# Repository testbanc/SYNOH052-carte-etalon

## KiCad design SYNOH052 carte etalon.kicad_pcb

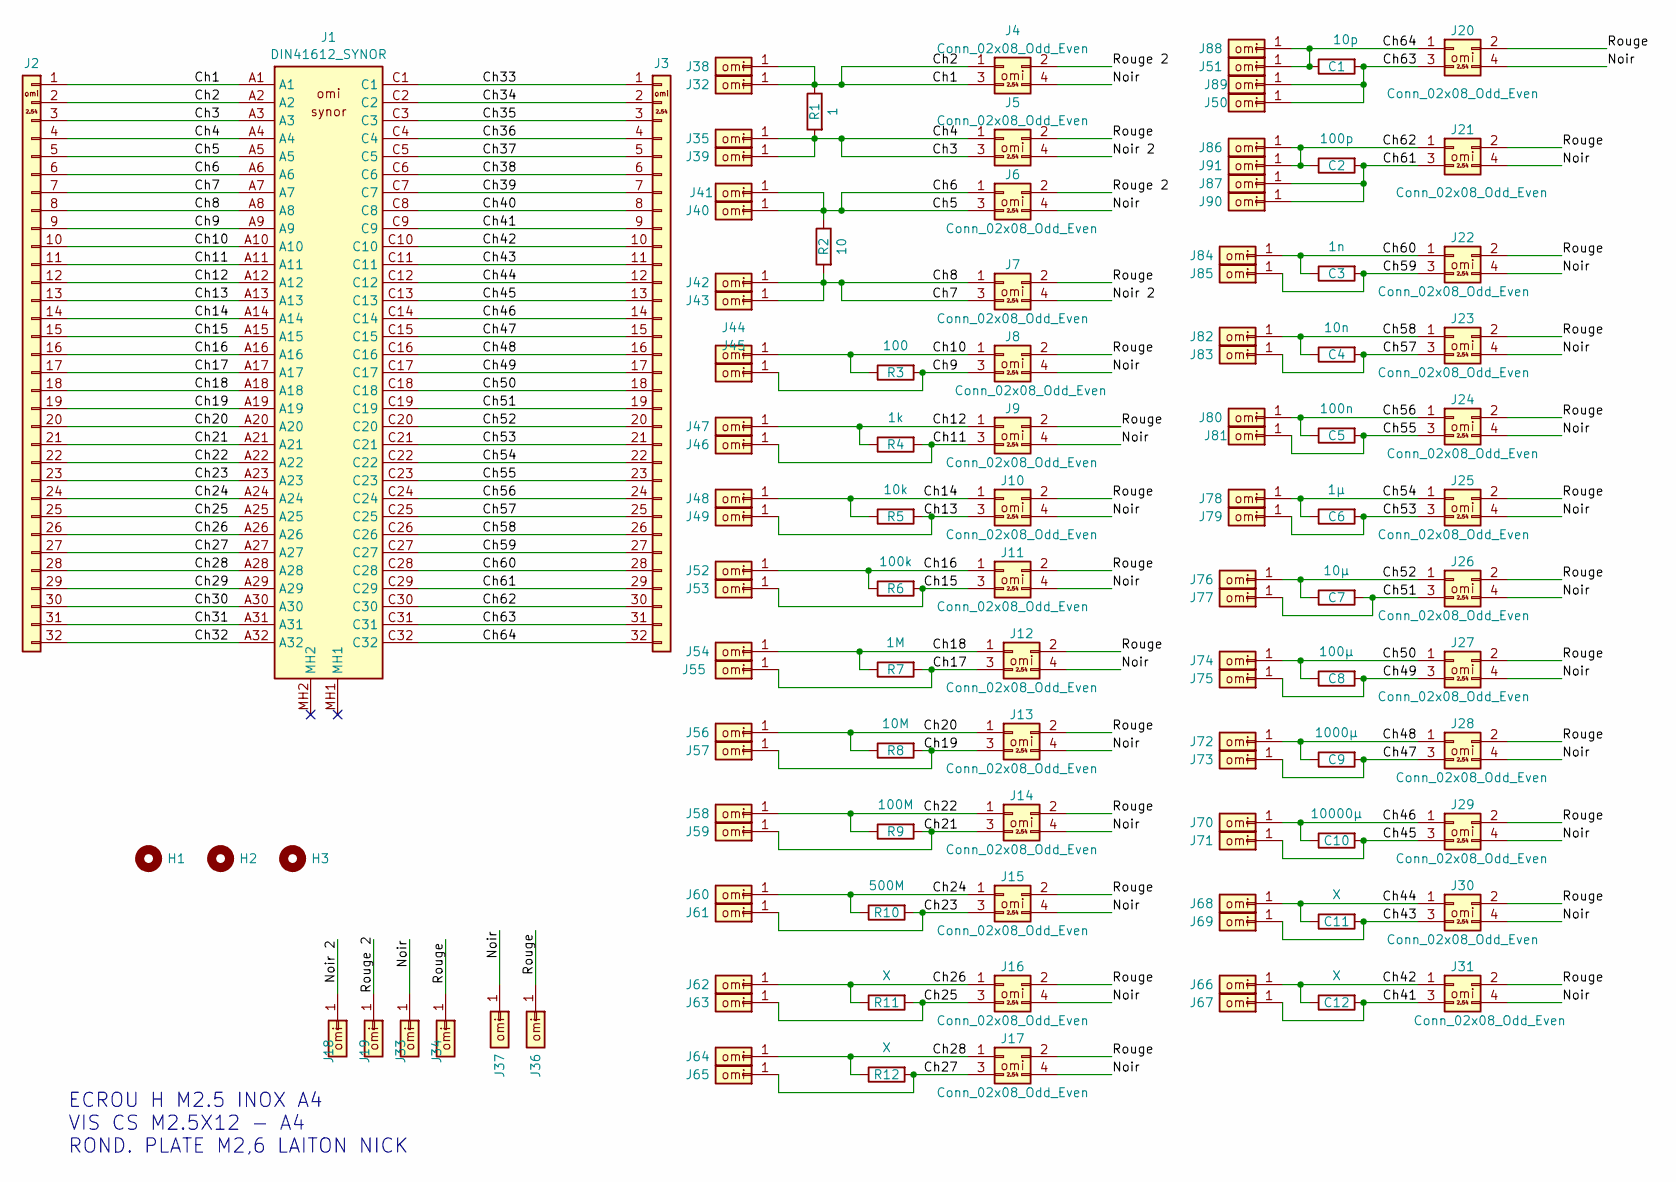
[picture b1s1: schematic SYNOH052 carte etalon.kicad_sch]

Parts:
C1: 10p; C_1206_3216Metric_Pad1.33x1.80mm_HandSolder
C2: 100p; C_1206_3216Metric_Pad1.33x1.80mm_HandSolder
C3: 1n; C_1206_3216Metric_Pad1.33x1.80mm_HandSolder
C4: 10n; C_1206_3216Metric_Pad1.33x1.80mm_HandSolder
C5: 100n; C_1206_3216Metric_Pad1.33x1.80mm_HandSolder
C6: 1µ; C_1206_3216Metric_Pad1.33x1.80mm_HandSolder
C7: 10µ; Condo_1_2x0_5 - Copie
C8: 100µ; Condo_1_7x0_5
C9: 1000µ; Condo_2x1
C10: 10000µ; Condo_4x2
C11, C12: X; C_1206_3216Metric_Pad1.33x1.80mm_HandSolder
H1, H2, H3: MountingHole; Fixation_M3
J1: DIN41612_SYNOR
J2, J3: Conn_01x32_P2.54mm_pinheader_vertical; PinHeader_1x32_P2.54mm_V_omi
J4, J5, J6, J7, J8, J9, J10, J11, J12, J13, J14, J15, J16, J17, J20, J21, J22, J23, J24, J25, J26, J27, J28, J29, J30, J31: Conn_02x08_Odd_Even; PinHeader_2x08_P2.54mm_V_omi
J18, J19, J32, J33, J34, J35, J36, J37, J38, J39, J40, J41, J42, J43, J44, J45, J46, J47, J48, J49, J50, J51, J52, J53, J54, J55, J56, J57, J58, J59, J60, J61, J62, J63, J64, J65, J66, J67, J68, J69, J70, J71, J72, J73, J74, J75, J76, J77, J78, J79, J80, J81, J82, J83, J84, J85, J86, J87, J88, J89, J90, J91: Conn_01x0_P2.54mm_pinheader_vertical; PinHeader_1x01_P2.54mm_V_omi
R1: 1; C_1206_3216Metric_Pad1.33x1.80mm_HandSolder
R2: 10; C_1206_3216Metric_Pad1.33x1.80mm_HandSolder
R3: 100; C_1206_3216Metric_Pad1.33x1.80mm_HandSolder
R4: 1k; C_1206_3216Metric_Pad1.33x1.80mm_HandSolder
R5: 10k; C_1206_3216Metric_Pad1.33x1.80mm_HandSolder
R6: 100k; C_1206_3216Metric_Pad1.33x1.80mm_HandSolder
R7: 1M; C_1206_3216Metric_Pad1.33x1.80mm_HandSolder
R8: 10M; C_1206_3216Metric_Pad1.33x1.80mm_HandSolder
R9: 100M; C_1206_3216Metric_Pad1.33x1.80mm_HandSolder
R10: 500M; C_1206_3216Metric_Pad1.33x1.80mm_HandSolder
R11, R12: X; C_1206_3216Metric_Pad1.33x1.80mm_HandSolder

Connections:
/Ch1: J1.A1, J1.A2, J2.1, J2.2, J4.1, J4.3, J32.1, J38.1, R1.1
/Ch3: J1.A3, J1.A4, J2.3, J2.4, J5.1, J5.3, J35.1, J39.1, R1.2
/Ch5: J1.A5, J1.A6, J2.5, J2.6, J6.1, J6.3, J40.1, J41.1, R2.1
/Ch7: J1.A7, J1.A8, J2.7, J2.8, J7.1, J7.3, J42.1, J43.1, R2.2
/Ch9: J1.A9, J2.9, J8.3, J45.1, R3.2
/Ch10: J1.A10, J2.10, J8.1, J44.1, R3.1
/Ch11: J1.A11, J2.11, J9.3, J46.1, R4.2
/Ch12: J1.A12, J2.12, J9.1, J47.1, R4.1
/Ch13: J1.A13, J2.13, J10.3, J49.1, R5.2
/Ch14: J1.A14, J2.14, J10.1, J48.1, R5.1
/Ch15: J1.A15, J2.15, J11.3, J53.1, R6.2
/Ch16: J1.A16, J2.16, J11.1, J52.1, R6.1
/Ch17: J1.A17, J2.17, J12.3, J55.1, R7.2
/Ch18: J1.A18, J2.18, J12.1, J54.1, R7.1
/Ch19: J1.A19, J2.19, J13.3, J57.1, R8.2
/Ch20: J1.A20, J2.20, J13.1, J56.1, R8.1
/Ch21: J1.A21, J2.21, J14.3, J59.1, R9.2
/Ch22: J1.A22, J2.22, J14.1, J58.1, R9.1
/Ch23: J1.A23, J2.23, J15.3, J61.1, R10.2
/Ch24: J1.A24, J2.24, J15.1, J60.1, R10.1
/Ch25: J1.A25, J2.25, J16.3, J63.1, R11.2
/Ch26: J1.A26, J2.26, J16.1, J62.1, R11.1
/Ch27: J1.A27, J2.27, J17.3, J65.1, R12.2
/Ch28: J1.A28, J2.28, J17.1, J64.1, R12.1
/Ch29: J1.A29, J2.29
/Ch30: J1.A30, J2.30
/Ch31: J1.A31, J2.31
/Ch32: J1.A32, J2.32
/Ch33: J1.C1, J3.1
/Ch34: J1.C2, J3.2
/Ch35: J1.C3, J3.3
/Ch36: J1.C4, J3.4
/Ch37: J1.C5, J3.5
/Ch38: J1.C6, J3.6
/Ch39: J1.C7, J3.7
/Ch40: J1.C8, J3.8
/Ch41: C12.2, J1.C9, J3.9, J31.3, J67.1
/Ch42: C12.1, J1.C10, J3.10, J31.1, J66.1
/Ch43: C11.2, J1.C11, J3.11, J30.3, J69.1
/Ch44: C11.1, J1.C12, J3.12, J30.1, J68.1
/Ch45: C10.2, J1.C13, J3.13, J29.3, J71.1
/Ch46: C10.1, J1.C14, J3.14, J29.1, J70.1
/Ch47: C9.2, J1.C15, J3.15, J28.3, J73.1
/Ch48: C9.1, J1.C16, J3.16, J28.1, J72.1
/Ch49: C8.2, J1.C17, J3.17, J27.3, J75.1
/Ch50: C8.1, J1.C18, J3.18, J27.1, J74.1
/Ch51: C7.2, J1.C19, J3.19, J26.3, J77.1
/Ch52: C7.1, J1.C20, J3.20, J26.1, J76.1
/Ch53: C6.2, J1.C21, J3.21, J25.3, J79.1
/Ch54: C6.1, J1.C22, J3.22, J25.1, J78.1
/Ch55: C5.2, J1.C23, J3.23, J24.3, J81.1
/Ch56: C5.1, J1.C24, J3.24, J24.1, J80.1
/Ch57: C4.2, J1.C25, J3.25, J23.3, J83.1
/Ch58: C4.1, J1.C26, J3.26, J23.1, J82.1
/Ch59: C3.2, J1.C27, J3.27, J22.3, J85.1
/Ch60: C3.1, J1.C28, J3.28, J22.1, J84.1
/Ch61: C2.2, J1.C29, J3.29, J21.3, J87.1, J90.1
/Ch62: C2.1, J1.C30, J3.30, J21.1, J86.1, J91.1
/Ch63: C1.2, J1.C31, J3.31, J20.3, J50.1, J89.1
/Ch64: C1.1, J1.C32, J3.32, J20.1, J51.1, J88.1
/Noir: J4.4, J6.4, J8.4, J9.4, J10.4, J11.4, J12.4, J13.4, J14.4, J15.4, J16.4, J17.4, J20.4, J21.4, J22.4, J23.4, J24.4, J25.4, J26.4, J27.4, J28.4, J29.4, J30.4, J31.4, J33.1, J37.1
/Noir 2: J5.4, J7.4, J18.1
/Rouge: J5.2, J7.2, J8.2, J9.2, J10.2, J11.2, J12.2, J13.2, J14.2, J15.2, J16.2, J17.2, J20.2, J21.2, J22.2, J23.2, J24.2, J25.2, J26.2, J27.2, J28.2, J29.2, J30.2, J31.2, J34.1, J36.1
/Rouge 2: J4.2, J6.2, J19.1

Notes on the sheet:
ECROU H M2.5 INOX A4 VIS CS M2.5X12 - A4 ROND. PLATE M2,6 LAITON NICK

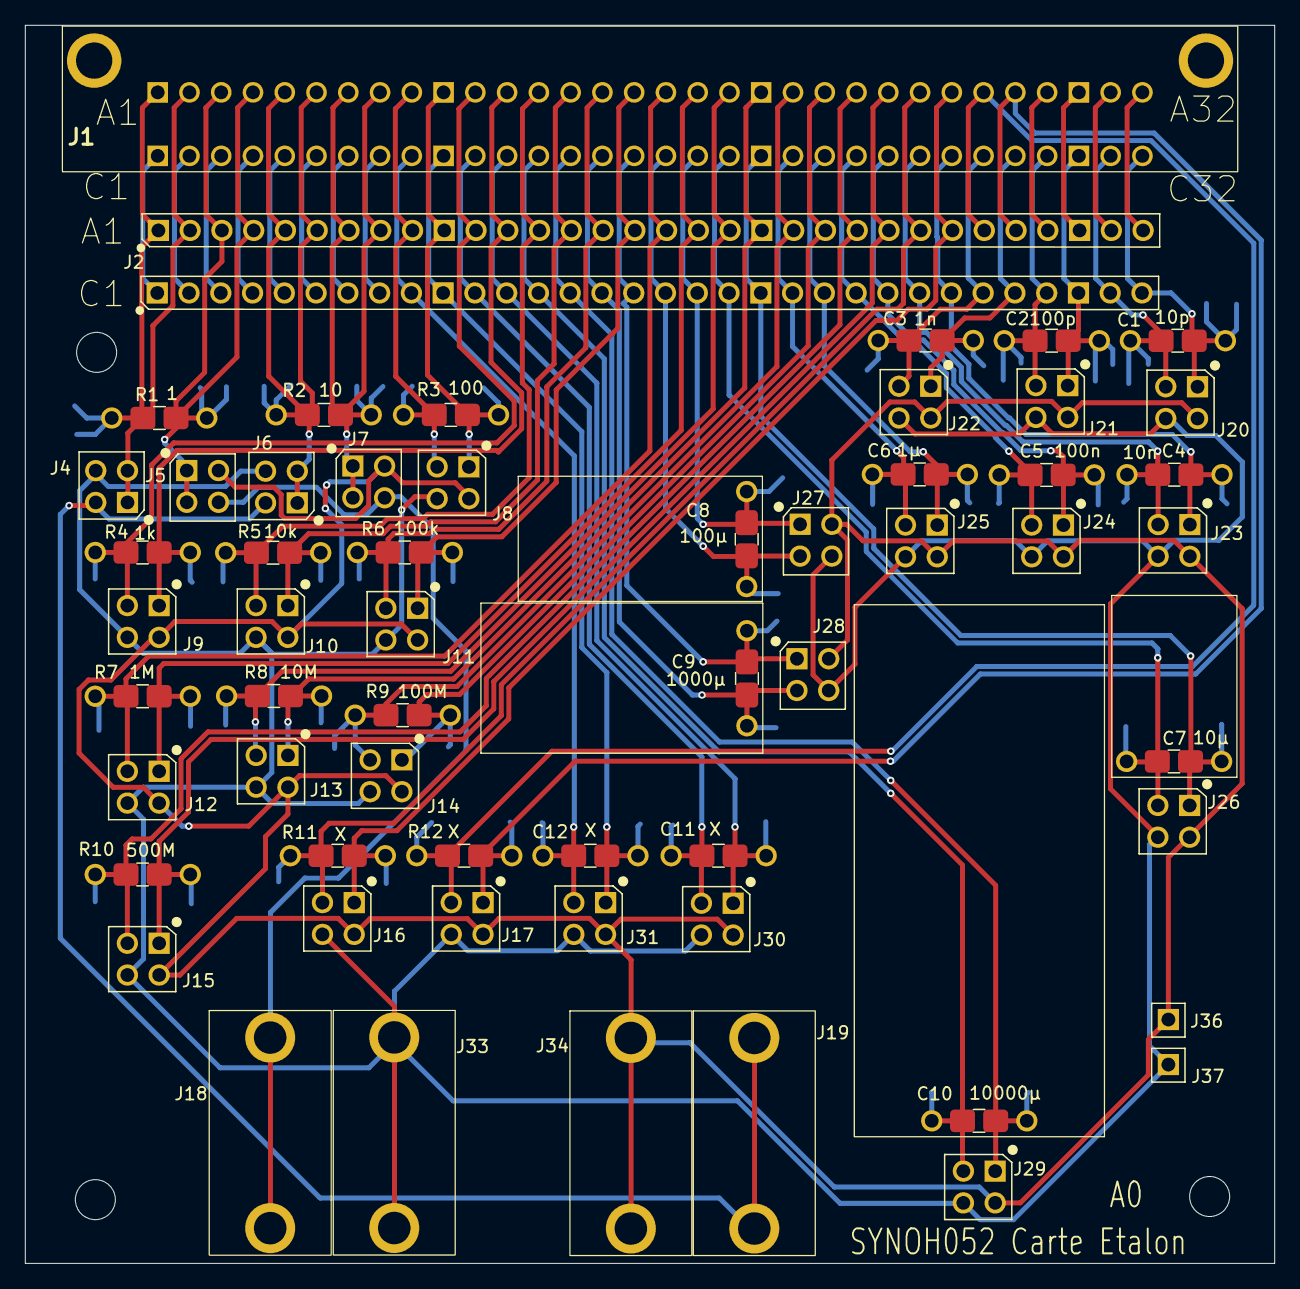
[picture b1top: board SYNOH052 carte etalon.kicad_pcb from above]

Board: 2 copper layers, 99.9 x 99.0 mm, 118 parts (0 on the bottom side), 64 nets.

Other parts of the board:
H4: MountingHole; Fixation_M3

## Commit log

2024-01-23 test
2024-03-13 13/03/2024 Signed-off-by: testbanc <banctest3@gmail.com>
2024-03-13 13/03/2024 , 10:27 Signed-off-by: testbanc <banctest3@gmail.com>
2024-03-21 version 21/03/2023 Signed-off-by: testbanc <banctest3@gmail.com>
